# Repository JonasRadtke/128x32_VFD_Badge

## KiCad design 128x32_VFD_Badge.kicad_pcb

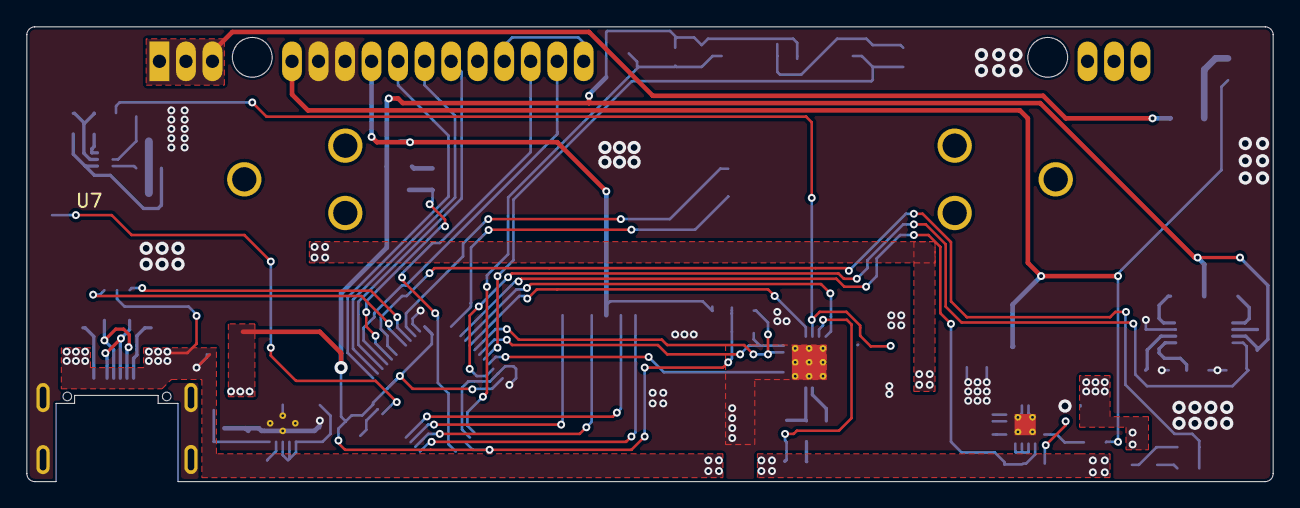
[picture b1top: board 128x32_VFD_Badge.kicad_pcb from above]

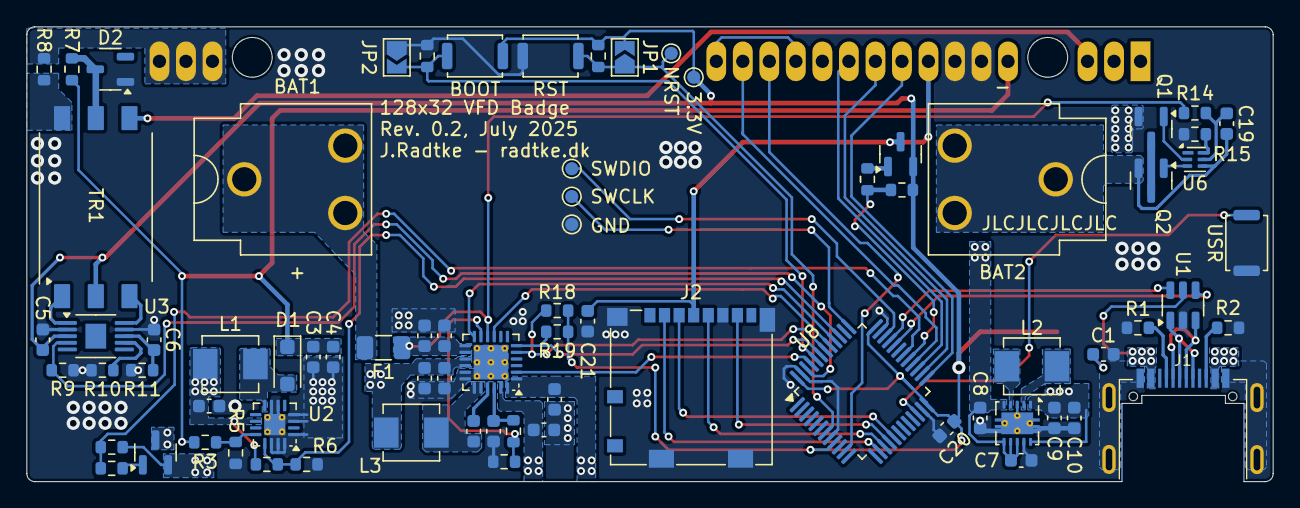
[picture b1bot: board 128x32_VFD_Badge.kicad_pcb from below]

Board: 2 copper layers, 94.0 x 34.3 mm, 77 parts (76 on the bottom side), 64 nets.

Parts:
BAT1: +; BatteryClip_Keystone_54_D16-19mm
BAT2: -; BatteryClip_Keystone_54_D16-19mm
C1: 100n; C_0603_1608Metric
C2, C7, C9, C10, C12, C13, C14, C16, C17: 10uF; C_0603_1608Metric
C3, C4, C6: 0.47uF; C_0603_1608Metric
C5, C8, C19, C20, C21: 100nF; C_0603_1608Metric
C11: 1uF; C_0603_1608Metric
C15: 47nF; C_0603_1608Metric
C18: 4.7uF; C_0603_1608Metric
D1: BAT46W; D_SOD-123F
D2: PZU84-B3V9R; SOT-23-3
F1: Fuse; Fuse_1206_3216Metric
J1: USB_C_Receptacle_USB2.0_16P; TYPE-C-31-M-14
J2: Micro_SD_Card_Det2; microSD_HC_Molex_104031-0811
JP1: NRST; SolderJumper-2_P1.3mm_Open_TrianglePad1.0x1.5mm
JP2: BOOT; SolderJumper-2_P1.3mm_Open_TrianglePad1.0x1.5mm
L1: 4.7uH; L_Vishay_IHLP-1616
L2, L3: 2.2uH; L_Vishay_IHLP-1616
Q1, Q2: CMSN3416K-HF; SOT-23
Q5, Q6: IRLML6401; SOT-23
R1, R2: 5,1k; R_0603_1608Metric
R3: 365k; R_0603_1608Metric
R4, R5, R7, R12, R13, R20, R21: 10k; R_0603_1608Metric
R6, R9, R16, R17: 100k; R_0603_1608Metric
R8: 15R; R_0603_1608Metric
R10, R11: 82k; R_0603_1608Metric
R14: 330R; R_0603_1608Metric
R15: 2.2k; R_0603_1608Metric
R18, R19: 4,7k; R_0603_1608Metric
R22, R23: 100R; R_0603_1608Metric
SW1, SW2, SW3: SKRKAEE020; SW_Push_SPST_NO_Alps_SKRK
TP1: 3.3V; TestPoint_Pad_D1.0mm
TP2: GND; TestPoint_Pad_D1.0mm
TP3: NRST; TestPoint_Pad_D1.0mm
TP4: SWDIO; TestPoint_Pad_D1.0mm
TP5: SWCLK; TestPoint_Pad_D1.0mm
TR1: 750316888; Transformer_Wuerth_750316888
U1: USBLC6-2SC6; SOT-23-6
U2: TPS61391; WQFN-16-1EP_3x3mm_P0.5mm_EP1.6x1.6mm_ThermalVias
U3: SN6507DGQ; HVSSOP-10-1EP_3x3mm_P0.5mm_EP1.57x1.88mm
U4: TPS63001; Texas_DRC0010J_ThermalVias
U5: BQ25619; WQFN-24-1EP_4x4mm_P0.5mm_EP2.6x2.6mm_ThermalVias
U6: BQ29737; WSON-6_1.5x1.5mm_P0.5mm
U7: MN12832L
U8: STM32U073CB; LQFP-48_7x7mm_P0.5mm

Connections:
+3.3V: C5.2, C9.1, C10.1, C20.1, JP1.2 (B), Q6.2 (S), R16.1, R18.1, R19.1, R21.1, SW1.1, TP1.1, TR1.2, U3.3 (VCC), U4.1 (VOUT), U4.10 (FB), U8.9 (VDDA), U8.24 (VDD), U8.36 (VDDUSB), U8.48 (VDD)
+5VBUS: C1.1, C11.1, J1.A4 (VBUS), J1.A9 (VBUS), J1.B4 (VBUS), J1.B9 (VBUS), U1.5 (VBUS), U5.1 (VAC), U5.24 (VBUS)
+45V: C3.1, C4.1, D1.1 (K), R3.1, R7.1, U7.6 (VDD2)
/3.3V Power Supply/VSYS: C7.1, C8.1, C13.1, C14.1, L3.2, U4.5 (VIN), U4.6 (EN), U4.7 (PS/SYNC), U4.8 (VINA), U5.15 (SYS), U5.16 (SYS)
/Charger/Cout: Q1.1 (G), U6.2 (Cout)
/Charger/Dout: Q2.1 (G), U6.3 (Dout)
/Charger/POWER_SEL: U5.2 (PSEL), U8.45 (PB8)
/Charger/QON: U5.12 (~QON), U8.40 (PB4)
/Charger/SCL: R18.2, U5.5 (SCL), U8.42 (PB6)
/Charger/SDA: R19.2, U5.6 (SDA), U8.43 (PB7)
/Charger/~CHARGE_EN: U5.9 (~CE), U8.41 (PB5)
/Controller & Display/3.3V_SWITCHED: C21.1, J2.4 (VDD), Q6.3 (D), U7.9 (VDD1)
/Controller & Display/5V_SWITCHED: C2.1, L1.1, Q5.3 (D), R4.1, U2.10 (VIN)
/Controller & Display/BLK: U7.10 (BLK), U8.25 (PB12)
/Controller & Display/BOOT0: JP2.2 (B), R17.1, SW1.2, U8.44 (PF3_BOOT0)
/Controller & Display/CLK: U7.15 (CLK), U8.11 (PA1)
/Controller & Display/CS: J2.2 (DAT3/CD), U8.14 (PA4)
/Controller & Display/DISP_EN: R4.2, R6.1, U2.13 (EN), U8.39 (PB3)
/Controller & Display/FIL_EN: R9.1, U3.4 (EN/UVLO), U8.46 (PB9)
/Controller & Display/Filament Driver/F1: TR1.4, U7.1 (F1), U7.2 (F1), U7.3 (F1)
/Controller & Display/Filament Driver/F2: R8.2, U7.36 (F2), U7.37 (F1), U7.38 (F1)
/Controller & Display/GCP: U7.12 (GCP), U8.27 (PB14)
/Controller & Display/LAT: U7.11 (LAT), U8.26 (PB13)
/Controller & Display/MISO: J2.7 (DAT0), U8.16 (PA6)
/Controller & Display/MOSI: J2.3 (CMD), U8.17 (PA7)
/Controller & Display/NRST: JP1.1 (A), R16.2, SW2.2, TP3.1, U8.7 (PF2_NRST)
/Controller & Display/SIN1: U7.16 (SIN1), U8.28 (PB15)
/Controller & Display/SIN2: U7.14 (SOUT1), U7.17 (SIN2)
/Controller & Display/SPI_SCK: J2.5 (CLK), U8.15 (PA5)
/Controller & Display/SWCLK: TP5.1, U8.37 (PA14_SWCLK)
/Controller & Display/SWDIO: TP4.1, U8.34 (PA13_SWDIO)
/Controller & Display/USB_DM: U1.4 (I/O2), U8.32 (PA11)
/Controller & Display/USB_DP: U1.6 (I/O1), U8.33 (PA12)
/Controller & Display/USR_BT: SW3.2, U8.22 (PB11)
/Controller & Display/~3.3V_EN: R21.2, R23.1, U8.29 (PA8)
/Controller & Display/~5V_EN: R20.2, R22.1, U8.30 (PA9)
BAT: C16.1, C17.1, F1.1, R14.1, U5.10 (BATSNS), U5.13 (BAT), U5.14 (BAT)
GND: C1.2, C2.2, C3.2, C4.2, C5.1, C6.2, C7.2, C8.2, C9.2, C10.2, C11.2, C12.2, C13.2, C14.2, C16.2, C17.2, C18.2, C20.2, C21.2, D2.1 (A), J1.A1 (GND), J1.A12 (GND), J1.B1 (GND), J1.B12 (GND), J1.S1 (SHIELD), J2.6 (VSS), J2.11 (SHIELD), JP2.1 (A), Q1.2 (S), R1.1, R2.1, R5.2, R6.2, R9.2, R10.2, R11.2, R12.2, R15.2, R17.2, SW2.1, SW3.1, TP2.1, U1.2 (GND), U2.1 (AVCC), U2.3 (MON2), U2.4 (MON1), U2.6 (MONIN), U2.7 (GND), U2.14 (AVCC), U2.15 (AVCC), U2.16 (AGND), U2.17 (PAD), U3.2 (GND), U3.9 (GND), U4.3 (PGND), U4.9 (GND), U4.11 (PGND), U5.17 (GND), U5.18 (GND), U5.25 (GND), U7.7 (VSS), U7.8 (VSS), U8.8 (VSSA), U8.23 (VSS), U8.35 (VSS), U8.47 (VSS)
GND1: BAT2.1, C19.2, Q2.2 (S), U6.4 (VSS)
unnamed: BAT1.1, F1.2
unnamed: C15.1, L3.1, U5.19 (SW), U5.20 (SW)
unnamed: D1.2 (A), L1.2, U2.8 (SW)
unnamed: D2.3 (K), R7.2, TR1.5
unnamed: J1.A5 (CC1), R1.2
unnamed: J1.B5 (CC2), R2.2
unnamed: J1.A6 (D+), J1.B6 (D+), U1.1 (I/O1)
unnamed: J1.A7 (D-), J1.B7 (D-), U1.3 (I/O2)
unnamed: Q1.3 (D), Q2.3 (D)
unnamed: Q5.1 (G), R22.2
unnamed: Q6.1 (G), R23.2
unnamed: R8.1, TR1.6
unnamed: R3.2, R5.1, U2.12 (FB)
unnamed: R10.1, U3.7 (CLK)
unnamed: C6.1, R11.1, U3.8 (SS/ILIM)
unnamed: TR1.1, U3.1 (SW1)
unnamed: TR1.3, U3.10 (SW2)
unnamed: L2.2, U4.4 (L1)
unnamed: L2.1, U4.2 (L2)
unnamed: C15.2, U5.21 (BTST)
unnamed: C18.1, R13.2, U5.22 (REGN)
unnamed: R12.1, R13.1, U5.11 (TS)
unnamed: C19.1, R14.2, U6.5 (BAT)
unnamed: R15.1, U6.6 (V-)
VPMID_5V: C12.1, Q5.2 (S), R20.1, U5.23 (PMID)

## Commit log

2025-05-15 Rev 0.1
2025-05-17 bitbanging
2025-07-06 spi_pins
    VFD over SPI
    3.3V and 5V over P-Channel Mosfet
